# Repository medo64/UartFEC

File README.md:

[UART Framework Expansion Card](https://medo64.com/uartframecard/)
==================================================================

This Framework laptop expansion card will show up on your system as a serial
device and allow for a non-isolated serial UART communication up to 3 Mbaud
baud rate.

Please note that this card is not using RS-232 but TTL (either 3.3V or 5V)
voltage levels (depending on solder-jumper position).

## UART Pinout

To connect to this board, one has to use a 3-pin JST XH connector. The following
table represents the pinout, pin 1 being on the left as looking into the
expansion card.

| # | Ref | Description                     |
|--:|:---:|---------------------------------|
| 1 | RXD | Receive (TTL: 5V or 3.3V)       |
| 2 | GND | Ground connection               |
| 3 | TXD | Transmit (TTL: 5V or 3.3V)      |

As power consumption is way below 10 mA, wires can be almost any AWG. I would
recommend using 24 AWG wire 0.25 mm² as they allow for greater compatibility
with other connectors.

## Supported Speeds

This board employs the FT232R as its UART chip, and consequently, it supports
all the baud rates this chip [can handle](https://ftdichip.com/Documents/AppNotes/AN232B-05_BaudRates.pdf).
The table below lists the standard baud rates.

| Baud rate |    Actual | Error |    Divisor |
|----------:|----------:|------:|-----------:|
|       300 |       300 | 0.00% |  10000.000 |
|       600 |       600 | 0.00% |   5000.000 |
|     1,200 |     1,200 | 0.00% |   2500.000 |
|     1,800 |     1,800 | 0.00% |   1666.625 |
|     2,400 |     2,400 | 0.00% |   1250.000 |
|     4,800 |     4,800 | 0.00% |    625.000 |
|     7,200 |     7,201 | 0.01% |    416.625 |
|     9,600 |     9,600 | 0.00% |    312.500 |
|    14,400 |    14,406 | 0.04% |    208.250 |
|    19,200 |    19,200 | 0.00% |    156.250 |
|    28,800 |    28,812 | 0.04% |    104.125 |
|    38,400 |    38,400 | 0.00% |     78.125 |
|    57,600 |    57,692 | 0.16% |     52.000 |
|   115,200 |   115,385 | 0.16% |     26.000 |
|   230,400 |   230,769 | 0.16% |     13.000 |
|   460,800 |   461,538 | 0.16% |      6.500 |
|   921,600 |   923,077 | 0.16% |      3.250 |
| 1,000,000 | 1,000,000 | 0.00% |      3.000 |

While chip does support baud rates up to 3 Mbaud, granularity of such rates
is severely limited.

---
*You can check my blog and other projects at [www.medo64.com](https://www.medo64.com/electronics/).*

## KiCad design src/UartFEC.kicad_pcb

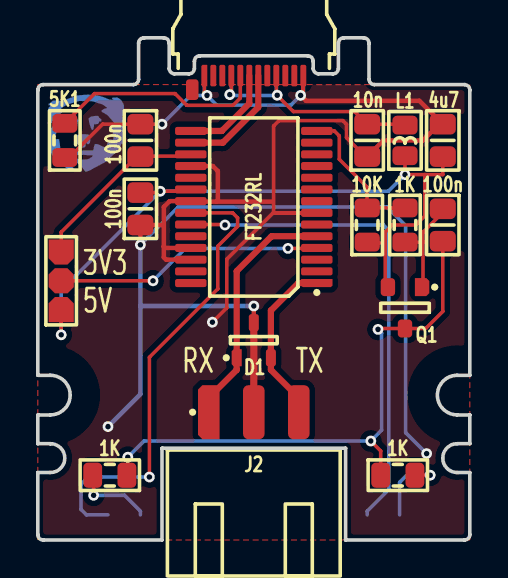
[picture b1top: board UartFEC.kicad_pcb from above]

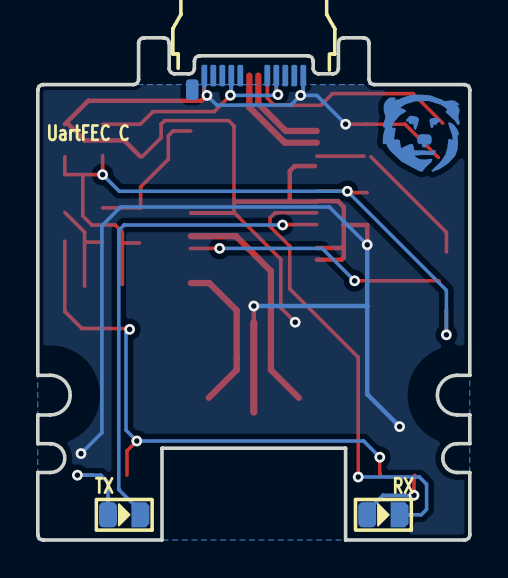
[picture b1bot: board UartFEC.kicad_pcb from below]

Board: 2 copper layers, 24.0 x 27.9 mm, 20 parts (3 on the bottom side), 17 nets.

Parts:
C1: 10n; C (0805)
C2, C3, C4: 100n; C (0805)
C5: 4u7; C (0805)
D1: SM05T1G; D TVS SM05T1G (SOT23-3)
DS1: RX; DS (0805)
DS2: TX; DS (0805)
ICON: Medo64; ICON Medo64
J1: 105444-0001; P USB C 3.2 Edge (24w)
J2: B3B-XH-A; J JST XH Edge [UART] (3w)
JP1: Jumper; JP Dual (1205)
L1: 600R; L (0805)
Q1: DMP3099L-13; Q MOSFET-P (SOT23-3)
R1, R2, R3: 1K; R (0805)
R4: 5K1; R (0805)
R5: 10K; R (0805)
U1: FT232RL; U Transciever UART FT232RL (SSOP-28)

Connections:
3V3: C3.2, JP1.3, U1.17
5V: C2.2, C5.2, JP1.1, L1.1, Q1.2, R5.1, U1.20
5V_SW: C4.2, Q1.3, R1.1, R2.1
A_CC: J1.A5, R4.2
GND: C1.1, C2.1, C3.1, C5.1, D1.3, J1.A1, J1.A12, J1.B01, J1.B12, J2.2, R4.1, U1.7, U1.18, U1.21, U1.25, U1.26
LED_RXD: DS1.1, U1.22
LED_RXD': DS1.2, R1.2
LED_TXD: DS2.1, U1.23
LED_TXD': DS2.2, R2.2
PWREN#: R3.1, R5.2, U1.14
PWREN#': C4.1, Q1.1, R3.2
RXD: D1.1, J2.1, U1.5
TXD: D1.2, J2.3, U1.1
USB_DM: J1.A7, U1.16
USB_DP: J1.A6, U1.15
USB_Vin: C1.2, J1.A4, J1.A9, J1.B04, J1.B09, L1.2
Vio: JP1.2, U1.4

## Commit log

2022-04-10 Added case
2022-04-11 Refactoring
2022-04-14 Updated text
2022-04-14 Updated components a bit
2022-04-18 Moving LEDs to corner
2022-04-20 Updated pinout to RXD GND TXD
2022-04-21 Refactoring a bit
2022-04-21 Refactoring power a bit
2022-04-21 Refactoring some more
2022-04-23 Adjusted shoulder
2022-05-06 Changed font to non-condensed variant
2022-05-07 Longer pads on type-C connector
2022-05-07 Removed extra CC2 resistor
2022-05-09 Turned LEDs around
2022-05-09 Updated case STLs
2022-06-21 Updated project name
2022-06-26 New release with covert I2C support
2022-06-26 Added missing fuse connection
2022-06-26 Changes sensor I2C address to 0x4F (was 0x48)
2022-06-26 Refactoring designators
2022-06-26 Added schematics
2022-06-26 Updated voltage output text
2022-06-26 Added output protection diode.
2022-06-26 Updated fuse model
2022-06-27 Changed shottky diode
2022-06-27 Corrected typo
2022-07-09 Adjusted shape for production reasons (slot width)
2022-08-15 Changed font
2023-09-18 Redesigned to use FT232R and removed I2C interface
2023-09-18 Added TVS protection
2023-10-08 Fixed FTDI digikey part number
2023-10-10 Larger silkscreen markings
2023-10-25 Fixed reset pin (was GND before; now flloating)
2023-10-25 Updated jumper and JST edge connector footprint
2023-10-25 Swapping L1 and 10nF location
2023-10-25 Added FTProg config files
2023-10-28 Updated templates
2023-10-30 Updated XML encoding
2023-11-02 Fixed CBUS definitions in part list
2023-11-04 Added RTS/CTS loopback
2023-11-13 Minor resistor move
2023-11-13 Moved LEDs to bottom
2023-12-26 Refactored LED control for standby
2023-12-26 Removed internal RTS/CTS connection
2023-12-30 Refactoring copper pour
2024-01-28 Added MOSFET
2024-01-28 Moved LEDs a bit
2024-01-31 Moved LEDs
2024-04-02 Updated connector designators
2024-04-28 Fixed refdes
